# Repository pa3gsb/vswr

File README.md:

VSWR - Module
==============================================

## Project:

For the radioberry this module gives the possibility for getting information about the vswr during transmit.

The module contains the possibility to measure the REF and FORWARD power.

Using a low speed i2c module makes it possible to read the data using the raspberry pi.

I have plans to add the reading:

-) to a seperate program to showing the measured data.
-) in the hpsdr emulator
-) in the pihpsdr plugin. 

Something about the setup.

The original design appeared in 1989 / 1990 SPRAT Magazine G-QRP
Also in the famous dutch QRP nieuwsbrief (NB 62) if found the article: "SWR METER ZONDER AFREGELING" door PAoWDW
I found it also in the openhpsdr ALEX project.

I did add the slow ADC i2c (as seen in the hermeslite version 2 design) 

## KICAD
Used KICAD to make the scheme and PCB.

Beside all this iam learning KICAD (stepped over from EAGLE). 
I like the KICAD program, much to learn, used start drawing a scheme. 
Add footprints and creating a PCB.

## Ordering
I ordered 6 January 2018 10 pcb at elecrow.

In the Netherlands it is possible to order at https://muxtronics.nl/ the components using the ShopCart from farnell.

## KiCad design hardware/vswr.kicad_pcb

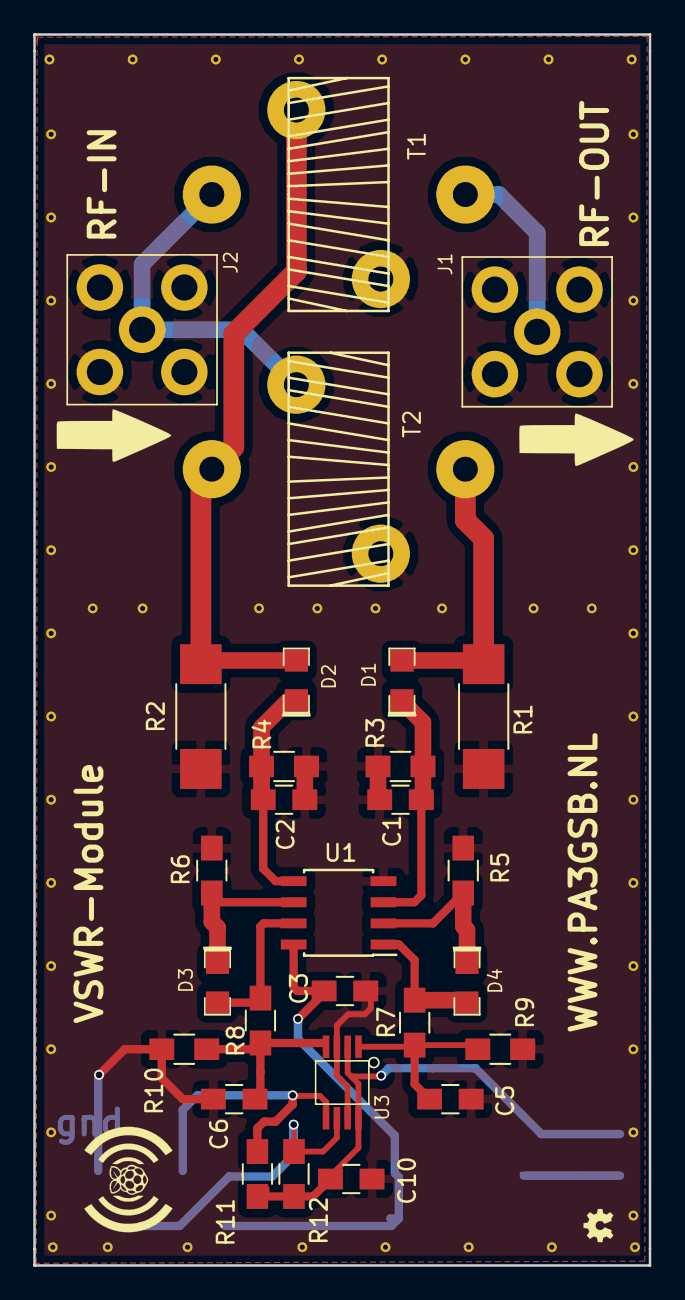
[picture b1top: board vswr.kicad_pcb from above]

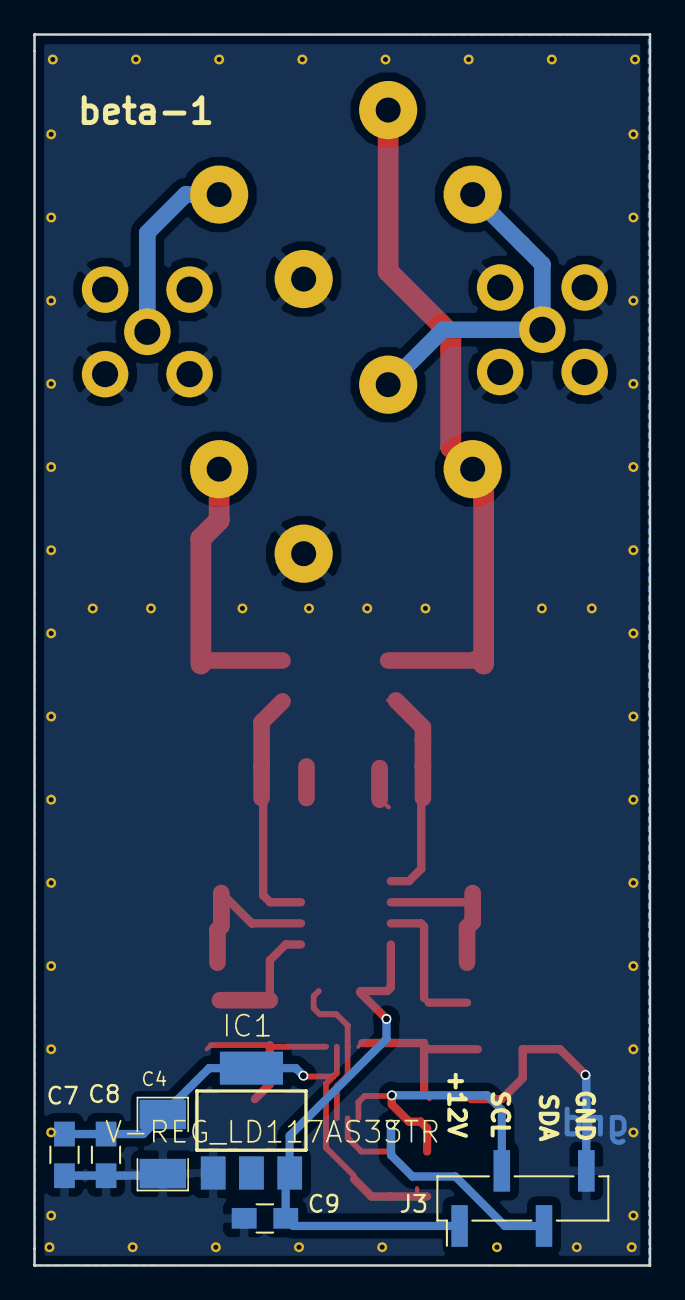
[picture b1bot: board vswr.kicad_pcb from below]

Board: 2 copper layers, 37.0 x 74.0 mm, 34 parts (6 on the bottom side), 17 nets.

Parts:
C1, C2, C3, C10: 100nF; C_0805_HandSoldering
C4: CP; SMD-1210
C5, C6: 10nF; C_0805_HandSoldering
C7, C8, C9: C; C_0805_HandSoldering
D1, D2, D3, D4: 1N5711W-7-F; 1N5711WS
IC1: V-REG_LD117AS33TR; V-REG_SOT223
J1, J2: CONN_COAXIAL; SMAVERT
J3: CONN_01X04; Pin_Header_Straight_1x04_Pitch2.54mm_SMD_Pin1Left
R1, R2: 51.1; R_2010_HandSoldering
R3, R4: 100K; R_0805_HandSoldering
R5, R6: 220K; R_0805_HandSoldering
R7, R8: 1K; R_0805_HandSoldering
R9, R10: 1K8; R_0805_HandSoldering
R11, R12: 4K7; R_0805_HandSoldering
T1, T2: FT50-43; T50-43_V_THT
U1: LMC6482; SOIC-8_3.9x4.9mm_Pitch1.27mm
U3: MAX11613

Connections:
+3V3: C4.1, C7.1, C8.1, C10.2, IC1.4, R11.1, R12.1, U3.2, U3.8
+12V: C3.2, C9.1, IC1.3, J3.1, U1.8
GND: C1.2, C2.1, C3.1, C4.2, C5.2, C6.1, C7.2, C8.2, C9.2, C10.1, IC1.1, J1.2, J2.2, J3.4, R1.1, R2.2, R3.2, R4.1, R5.1, R6.1, R9.2, R10.1, T1.3, T2.4, U1.4, U3.3, U3.7
unnamed: C1.1, D1.2, R3.1, U1.3
unnamed: C2.2, D2.2, R4.2, U1.5
unnamed: C5.1, R7.1, R9.1, U3.1
unnamed: C6.2, R8.1, R10.2, U3.4
unnamed: D1.1, R1.2, T2.1
unnamed: D2.1, R2.1, T1.4, T2.2
unnamed: D3.1, R8.2, U1.7
unnamed: D3.2, R6.2, U1.6
unnamed: D4.1, R7.2, U1.1
unnamed: D4.2, R5.2, U1.2
unnamed: J1.1, T1.2
unnamed: J2.1, T1.1, T2.3
SCL: J3.2, R11.2, U3.5
SDA: J3.3, R12.2, U3.6

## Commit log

2018-01-06 hardware map aangemaakt
2018-01-06 readme added
2018-09-07 software using terminal for checking
2018-12-31 user interface toegevoegd
